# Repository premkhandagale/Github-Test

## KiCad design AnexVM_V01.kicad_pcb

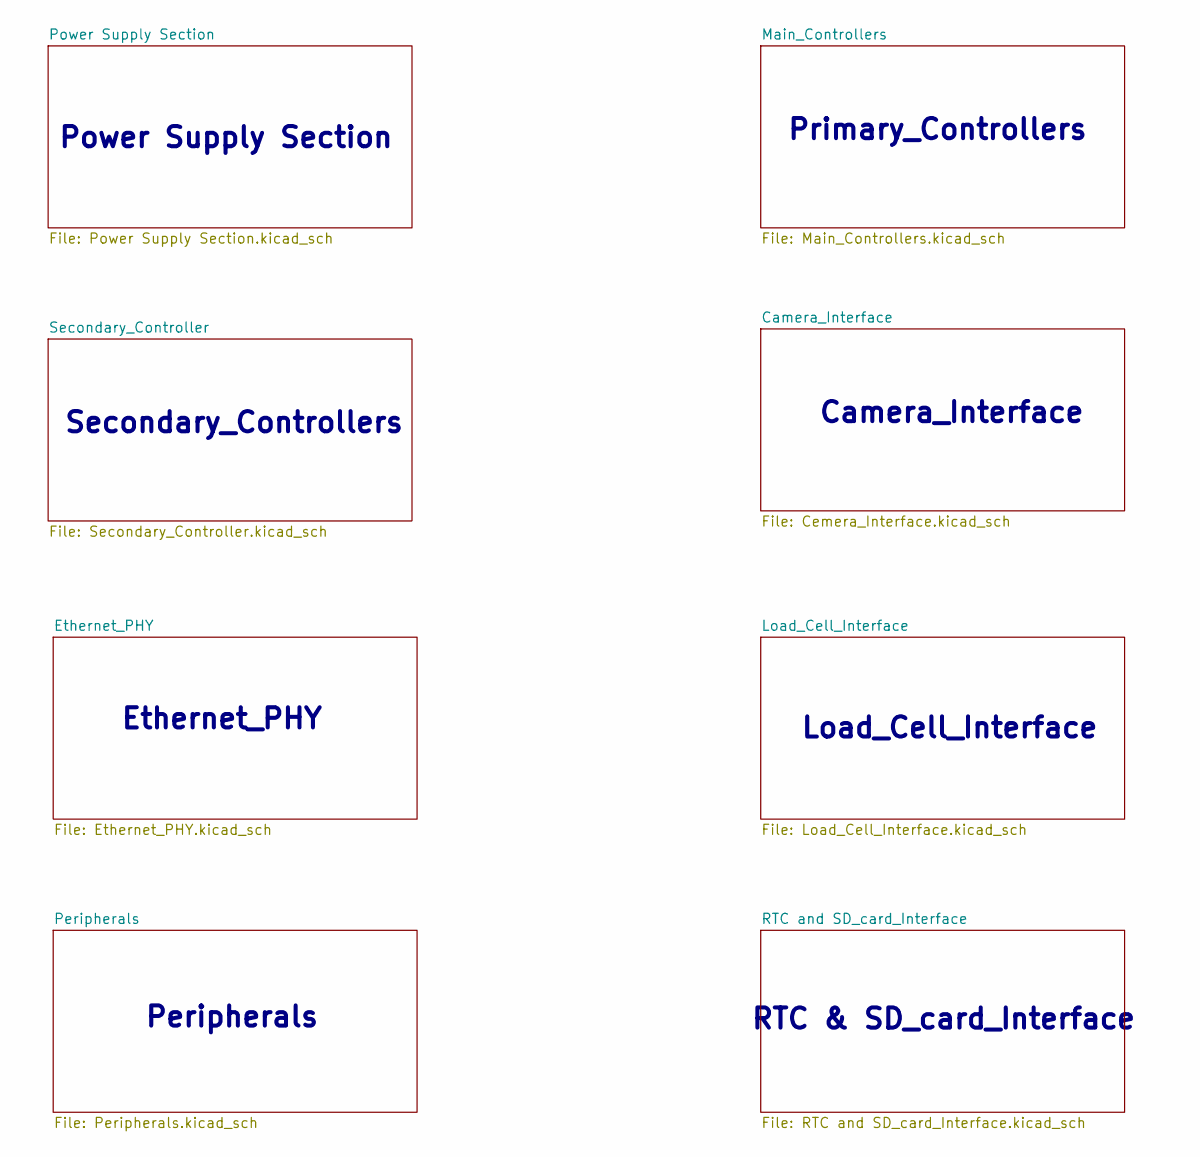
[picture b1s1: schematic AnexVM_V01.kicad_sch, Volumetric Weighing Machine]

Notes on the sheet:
Secondary_Controllers
Peripherals
Primary_Controllers
Load_Cell_Interface
Power Supply Section
Camera_Interface
Ethernet_PHY
RTC & SD_card_Interface

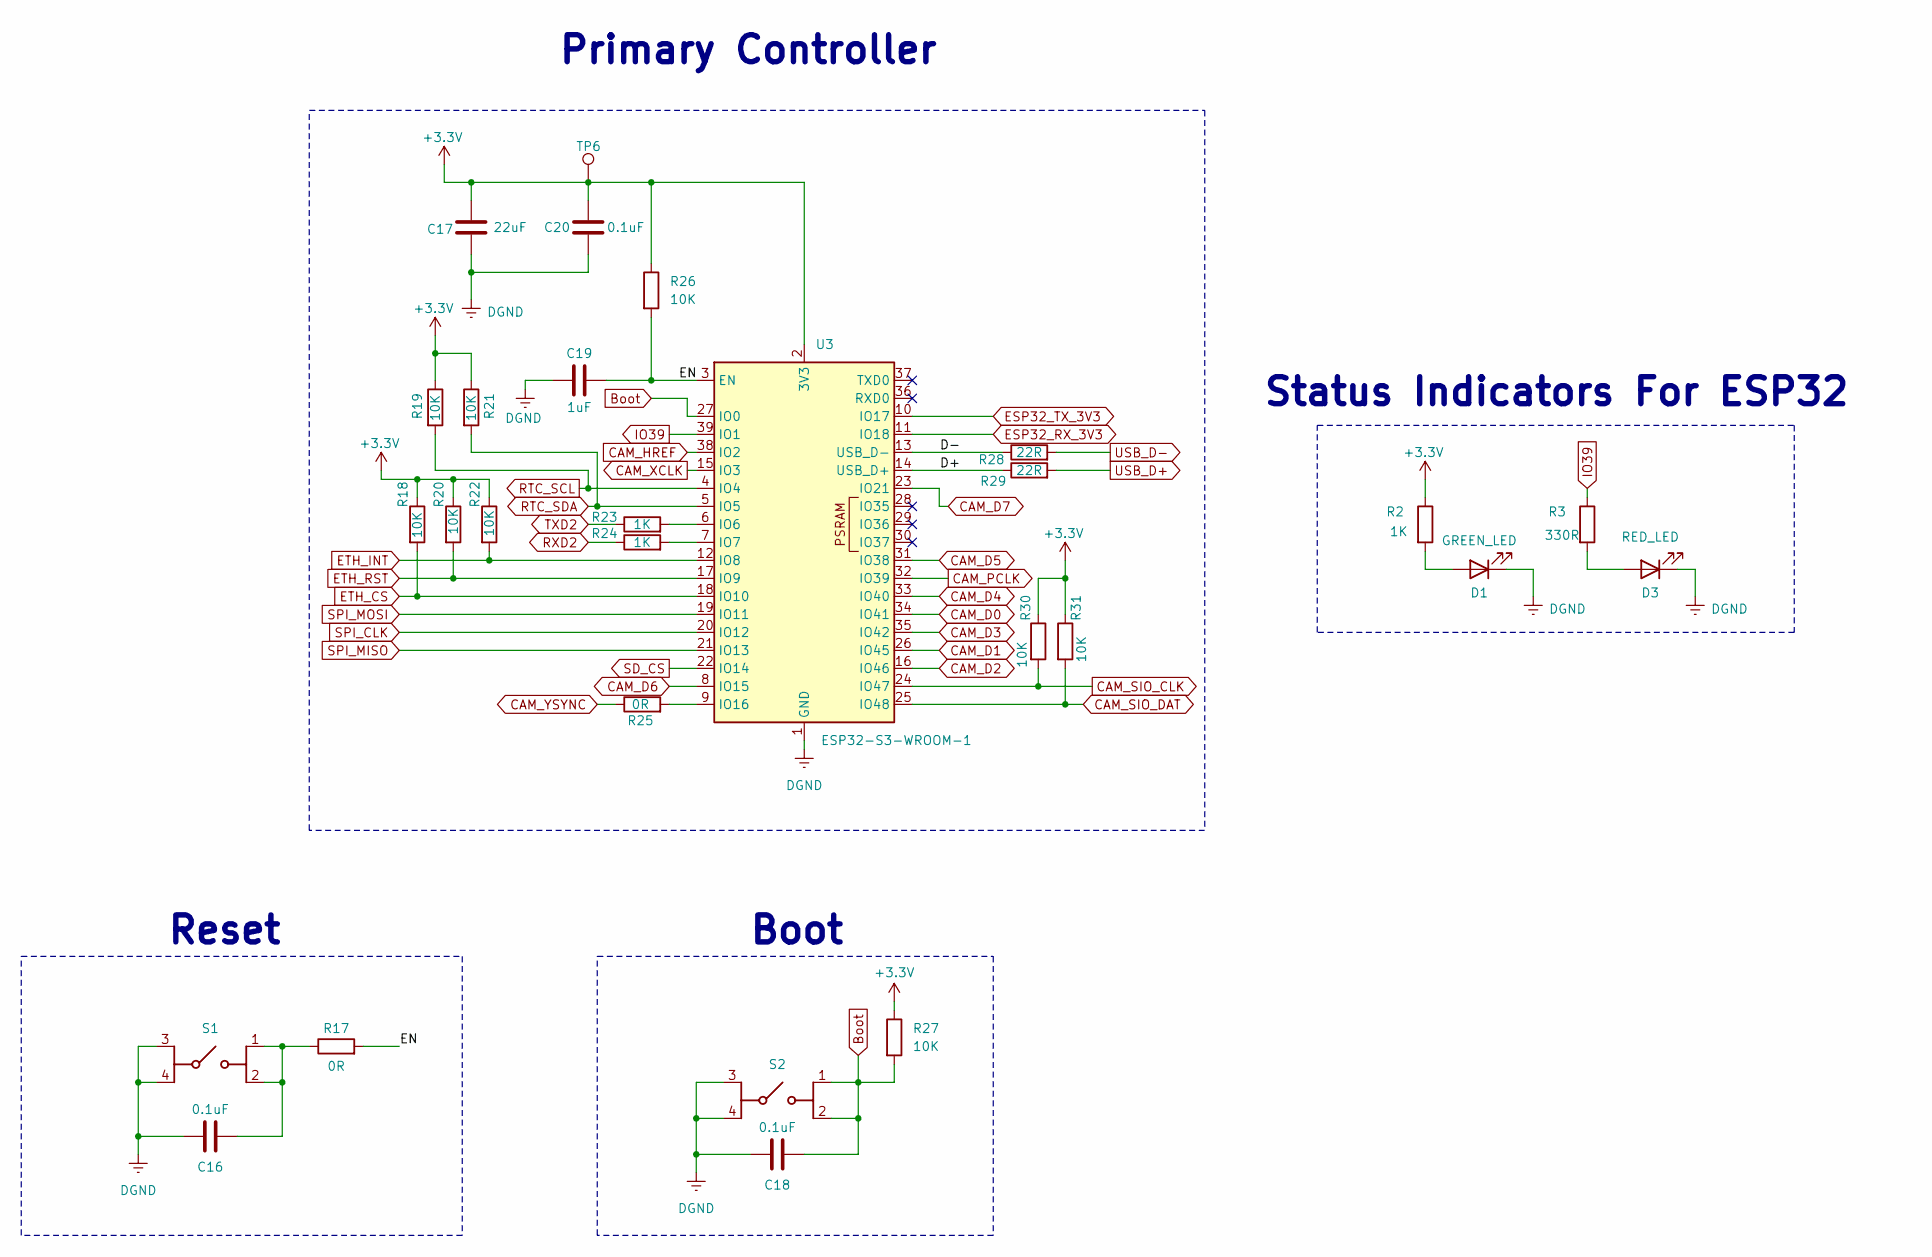
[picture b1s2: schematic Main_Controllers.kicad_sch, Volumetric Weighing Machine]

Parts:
C16, C18, C20: 0.1uF; C_0603_1608Metric
C17: 22uF; C_0805_2012Metric
C19: 1uF; C_0603_1608Metric
D1: GREEN_LED; LED_D3.0mm
D3: RED_LED; LED_D3.0mm
R2, R23, R24: 1K; R_0603_1608Metric
R3: 330R; R_0603_1608Metric
R17, R25: 0R; R_0603_1608Metric
R18, R19, R20, R21, R22, R26, R27, R30, R31: 10K; R_0603_1608Metric
R28, R29: 22R; R_0603_1608Metric
S1, S2: PTS647SK38SMTR2_LFS; SW_SPST_PTS647_Sx38; Manufacturer_Part_Number PTS647SK38SMTR2 LFS
TP6: TestPoint; TestPoint_Pad_D1.0mm
U3: ESP32-S3-WROOM-1

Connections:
+3.3V: C17.1, C20.1, R2.1, R18.1, R19.1, R20.1, R21.1, R22.1, R26.1, R27.1, R30.1, R31.1, TP6.1, U3.2 (3V3); also elsewhere on the board
/Main_Controllers/D+: R29.1, U3.14 (USB_D+)
/Main_Controllers/D-: R28.1, U3.13 (USB_D-)
/Main_Controllers/EN: C19.2, R17.2, R26.2, U3.3 (EN)
Boot: C18.2, R27.2, S2.1 (NO_1), S2.2 (NO_2), U3.27 (IO0)
CAM_D0: U3.34 (IO41); also elsewhere on the board
CAM_D1: U3.26 (IO45); also elsewhere on the board
CAM_D2: U3.16 (IO46); also elsewhere on the board
CAM_D3: U3.35 (IO42); also elsewhere on the board
CAM_D4: U3.33 (IO40); also elsewhere on the board
CAM_D5: U3.31 (IO38); also elsewhere on the board
CAM_D6: U3.8 (IO15); also elsewhere on the board
CAM_D7: U3.23 (IO21); also elsewhere on the board
CAM_HREF: U3.38 (IO2); also elsewhere on the board
CAM_PCLK: U3.32 (IO39); also elsewhere on the board
CAM_SIO_CLK: R30.2, U3.24 (IO47); also elsewhere on the board
CAM_SIO_DAT: R31.2, U3.25 (IO48); also elsewhere on the board
CAM_XCLK: U3.15 (IO3); also elsewhere on the board
CAM_YSYNC: R25.1; also elsewhere on the board
DGND: C16.1, C17.2, C18.1, C19.1, C20.2, D1.1 (K), D3.1 (K), S1.3 (COM_1), S1.4 (COM_2), S2.3 (COM_1), S2.4 (COM_2), U3.1 (GND), U3.40 (GND), U3.41 (GND); also elsewhere on the board
ESP32_RX_3V3: U3.11 (IO18); also elsewhere on the board
ESP32_TX_3V3: U3.10 (IO17); also elsewhere on the board
ETH_CS: R18.2, U3.18 (IO10); also elsewhere on the board
ETH_INT: R22.2, U3.12 (IO8); also elsewhere on the board
ETH_RST: R20.2, U3.17 (IO9); also elsewhere on the board
IO39: R3.1, U3.39 (IO1)
unnamed: D1.2 (A), R2.2
unnamed: D3.2 (A), R3.2
unnamed: C16.2, R17.1, S1.1 (NO_1), S1.2 (NO_2)
unnamed: R23.2, U3.6 (IO6)
unnamed: R24.2, U3.7 (IO7)
unnamed: R25.2, U3.9 (IO16)
RTC_SCL: R19.2, U3.4 (IO4); also elsewhere on the board
RTC_SDA: R21.2, U3.5 (IO5); also elsewhere on the board
RXD2: R24.1; also elsewhere on the board
SD_CS: U3.22 (IO14); also elsewhere on the board
SPI_CLK: U3.20 (IO12); also elsewhere on the board
SPI_MISO: U3.21 (IO13); also elsewhere on the board
SPI_MOSI: U3.19 (IO11); also elsewhere on the board
TXD2: R23.1; also elsewhere on the board
USB_D+: R29.2; also elsewhere on the board
USB_D-: R28.2; also elsewhere on the board

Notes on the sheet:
Reset
Primary Controller
Boot
Status Indicators For ESP32

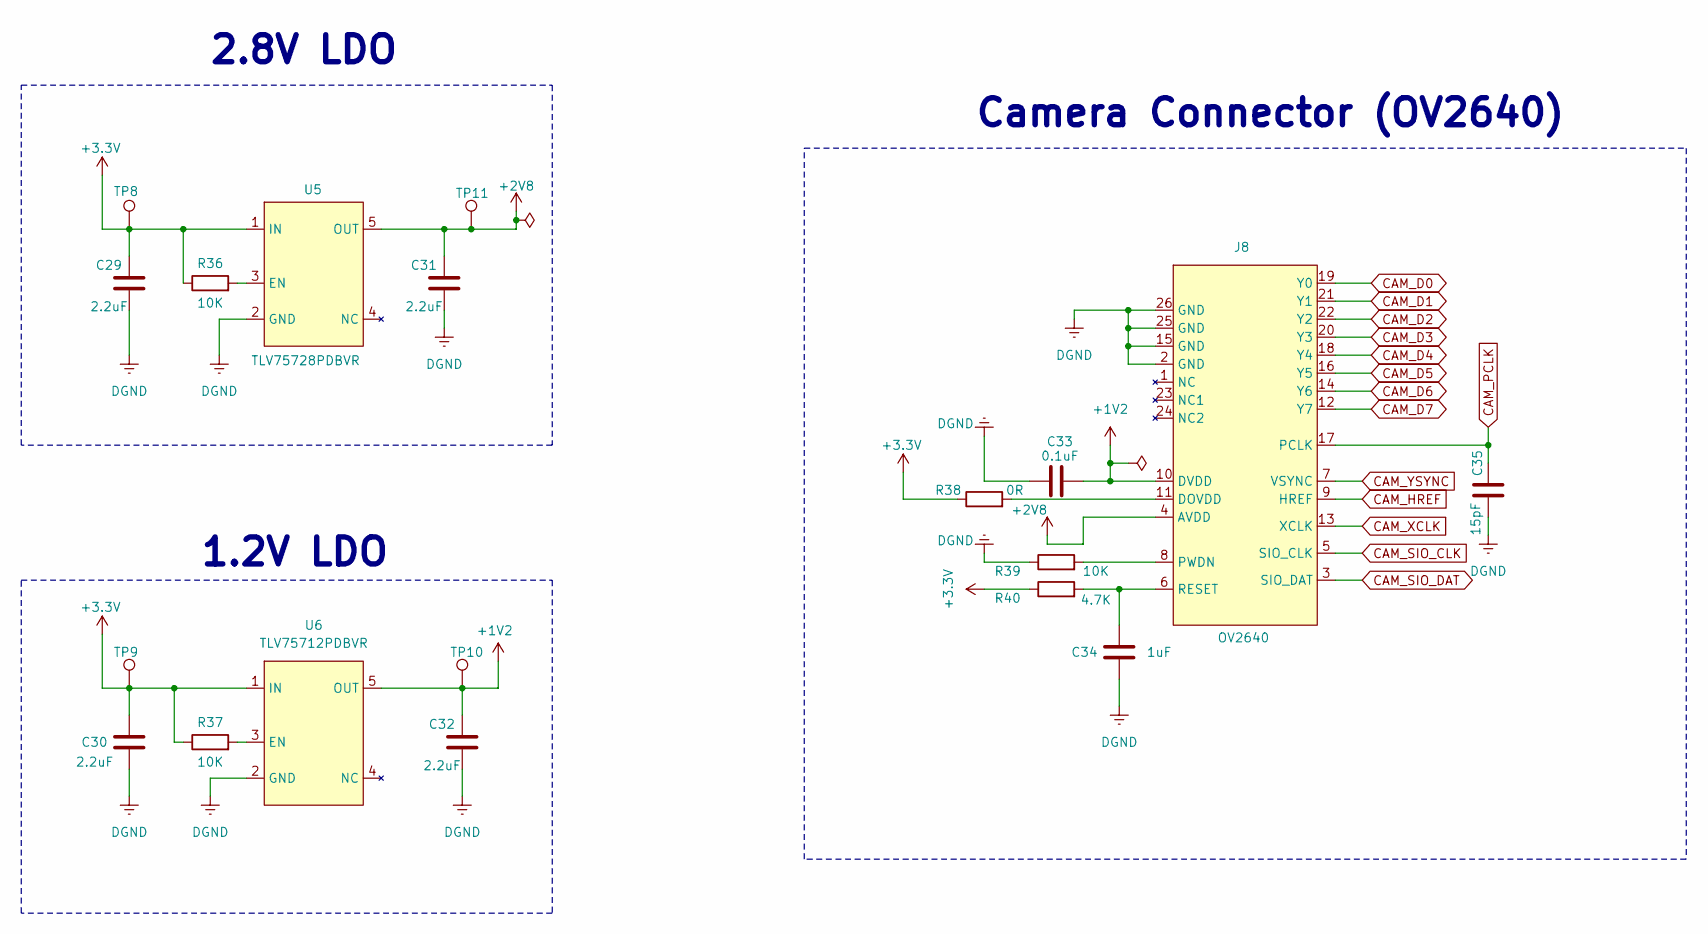
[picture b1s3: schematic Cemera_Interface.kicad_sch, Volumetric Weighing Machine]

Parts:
C29, C30, C31, C32: 2.2uF; C_0603_1608Metric
C33: 0.1uF; C_0603_1608Metric
C34: 1uF; C_0603_1608Metric
C35: 15pF; C_0603_1608Metric
J8: OV2640; Hirose_FH12-24S-0.5SH_1x24-1MP_P0.50mm_Horizontal
R36, R37, R39: 10K; R_0603_1608Metric
R38: 0R; R_0603_1608Metric
R40: 4.7K; R_0603_1608Metric
TP8, TP9, TP10, TP11: TestPoint; TestPoint_Pad_D1.0mm
U5: TLV75728PDBVR; SOT-23-5
U6: TLV75712PDBVR; SOT-23-5

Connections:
+1V2: C32.1, C33.2, J8.10 (DVDD), TP10.1, U6.5 (OUT)
+2V8: C31.1, J8.4 (AVDD), TP11.1, U5.5 (OUT)
+3.3V: C29.1, C30.1, R36.1, R37.1, R38.1, R40.1, TP8.1, TP9.1, U5.1 (IN), U6.1 (IN); also elsewhere on the board
CAM_D0: J8.19 (Y0); also elsewhere on the board
CAM_D1: J8.21 (Y1); also elsewhere on the board
CAM_D2: J8.22 (Y2); also elsewhere on the board
CAM_D3: J8.20 (Y3); also elsewhere on the board
CAM_D4: J8.18 (Y4); also elsewhere on the board
CAM_D5: J8.16 (Y5); also elsewhere on the board
CAM_D6: J8.14 (Y6); also elsewhere on the board
CAM_D7: J8.12 (Y7); also elsewhere on the board
CAM_HREF: J8.9 (HREF); also elsewhere on the board
CAM_PCLK: C35.1, J8.17 (PCLK); also elsewhere on the board
CAM_SIO_CLK: J8.5 (SIO_CLK); also elsewhere on the board
CAM_SIO_DAT: J8.3 (SIO_DAT); also elsewhere on the board
CAM_XCLK: J8.13 (XCLK); also elsewhere on the board
CAM_YSYNC: J8.7 (VSYNC); also elsewhere on the board
DGND: C29.2, C30.2, C31.2, C32.2, C33.1, C34.2, C35.2, J8.2 (GND), J8.15 (GND), J8.25 (GND), J8.26 (GND), R39.1, U5.2 (GND), U6.2 (GND); also elsewhere on the board
unnamed: J8.11 (DOVDD), R38.2
unnamed: J8.8 (PWDN), R39.2
unnamed: C34.1, J8.6 (RESET), R40.2
unnamed: R36.2, U5.3 (EN)
unnamed: R37.2, U6.3 (EN)

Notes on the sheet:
Camera Connector (OV2640)
2.8V LDO
1.2V LDO

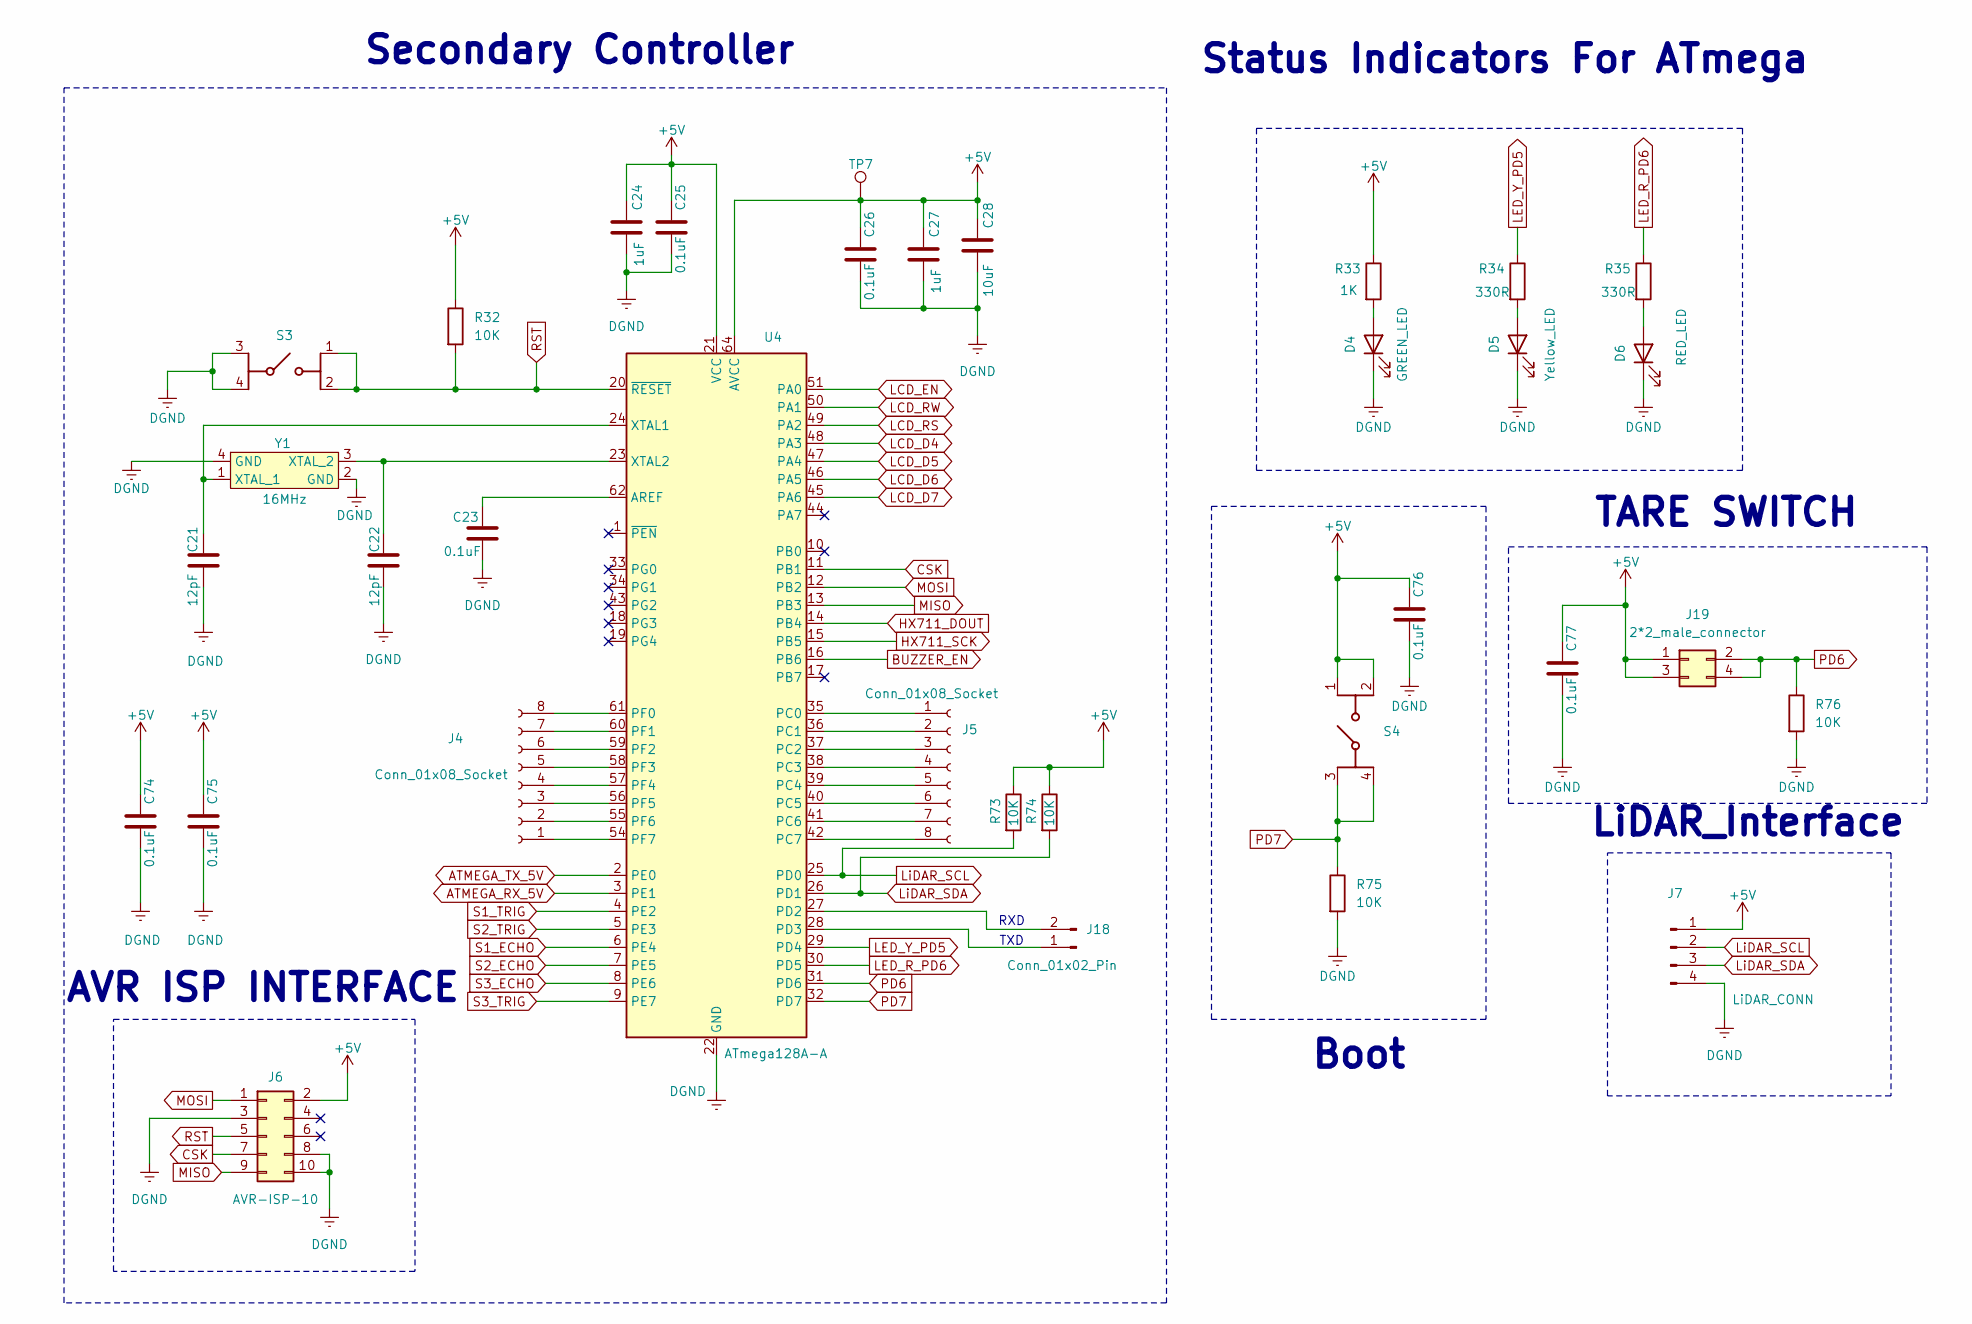
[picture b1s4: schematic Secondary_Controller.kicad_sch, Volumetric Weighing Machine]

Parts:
C21, C22: 12pF; C_0603_1608Metric
C23, C25, C26, C74, C75, C76, C77: 0.1uF; C_0603_1608Metric
C24, C27: 1uF; C_0603_1608Metric
C28: 10uF; C_0805_2012Metric
D4: GREEN_LED; LED_D3.0mm
D5: Yellow_LED; LED_D3.0mm
D6: RED_LED; LED_D3.0mm
J4, J5: Conn_01x08_Socket; PinSocket_1x08_P2.54mm_Vertical
J6: AVR-ISP-10; PinHeader_2x05_P2.54mm_Vertical
J7: LiDAR_CONN; PinHeader_1x04_P2.54mm_Vertical
J18: Conn_01x02_Pin; PinHeader_1x02_P2.54mm_Vertical
J19: 2*2_male_connector; PinHeader_2x02_P2.54mm_Vertical
R32, R73, R74, R75, R76: 10K; R_0603_1608Metric
R33: 1K; R_0603_1608Metric
R34, R35: 330R; R_0603_1608Metric
S3, S4: PTS647SK38SMTR2_LFS; SW_SPST_PTS647_Sx38; Manufacturer_Part_Number PTS647SK38SMTR2 LFS
TP7: TestPoint; TestPoint_Pad_D1.0mm
U4: ATmega128A-A; TQFP-64_14x14mm_P0.8mm
Y1: 16MHz; Crystal_SMD_3225-4Pin_3.2x2.5mm

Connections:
+5V: C24.1, C25.1, C26.1, C27.1, C28.1, C74.1, C75.1, C76.1, C77.1, J6.2 (Pin_b2), J7.1, J19.1 (NO1), J19.3 (N02), R32.1, R33.1, R73.1, R74.1, S4.1 (NO_1), S4.2 (NO_2), TP7.1, U4.21 (VCC), U4.52 (VCC), U4.64 (AVCC); also elsewhere on the board
ATMEGA_RX_5V: U4.3 (PE1); also elsewhere on the board
ATMEGA_TX_5V: U4.2 (PE0); also elsewhere on the board
BUZZER_EN: U4.16 (PB6); also elsewhere on the board
CSK: J6.7 (Pin_z8), U4.11 (PB1)
DGND: C21.2, C22.2, C23.2, C24.2, C25.2, C26.2, C27.2, C28.2, C74.2, C75.2, C76.2, C77.2, D4.1 (K), D5.1 (K), D6.1 (K), J6.3 (Pin_z4), J6.8 (Pin_b8), J6.10 (Pin_b10), J7.4, R75.2, R76.2, S3.3 (COM_1), S3.4 (COM_2), U4.22 (GND), U4.53 (GND), U4.63 (GND), Y1.2 (GND), Y1.4 (GND); also elsewhere on the board
HX711_DOUT: U4.14 (PB4); also elsewhere on the board
HX711_SCK: U4.15 (PB5); also elsewhere on the board
LCD_D4: U4.48 (PA3); also elsewhere on the board
LCD_D5: U4.47 (PA4); also elsewhere on the board
LCD_D6: U4.46 (PA5); also elsewhere on the board
LCD_D7: U4.45 (PA6); also elsewhere on the board
LCD_EN: U4.51 (PA0); also elsewhere on the board
LCD_RS: U4.49 (PA2); also elsewhere on the board
LCD_RW: U4.50 (PA1); also elsewhere on the board
LED_R_PD6: R35.1, U4.30 (PD5)
LED_Y_PD5: R34.1, U4.29 (PD4)
LiDAR_SCL: J7.2, R73.2, U4.25 (PD0)
LiDAR_SDA: J7.3, R74.2, U4.26 (PD1)
MISO: J6.9 (Pin_z10), U4.13 (PB3)
MOSI: J6.1 (Pin_z2), U4.12 (PB2)
unnamed: D4.2 (A), R33.2
unnamed: D5.2 (A), R34.2
unnamed: D6.2 (A), R35.2
unnamed: J4.1, U4.54 (PF7)
unnamed: J4.2, U4.55 (PF6)
unnamed: J4.3, U4.56 (PF5)
unnamed: J4.4, U4.57 (PF4)
unnamed: J4.5, U4.58 (PF3)
unnamed: J4.6, U4.59 (PF2)
unnamed: J4.7, U4.60 (PF1)
unnamed: J4.8, U4.61 (PF0)
unnamed: J5.1, U4.35 (PC0)
unnamed: J5.2, U4.36 (PC1)
unnamed: J5.3, U4.37 (PC2)
unnamed: J5.4, U4.38 (PC3)
unnamed: J5.5, U4.39 (PC4)
unnamed: J5.6, U4.40 (PC5)
unnamed: J5.7, U4.41 (PC6)
unnamed: J5.8, U4.42 (PC7)
unnamed: J18.1, U4.28 (PD3)
unnamed: J18.2, U4.27 (PD2)
unnamed: C23.1, U4.62 (AREF)
unnamed: C21.1, U4.24 (XTAL1), Y1.1 (XTAL_1)
unnamed: C22.1, U4.23 (XTAL2), Y1.3 (XTAL_2)
PD6: J19.2 (NC1), J19.4 (NC2), R76.1, U4.31 (PD6)
PD7: R75.1, S4.3 (COM_1), S4.4 (COM_2), U4.32 (PD7)
RST: J6.5 (Pin_z6), R32.2, S3.1 (NO_1), S3.2 (NO_2), U4.20 (~RESET)
S1_ECHO: U4.6 (PE4); also elsewhere on the board
S1_TRIG: U4.4 (PE2); also elsewhere on the board
S2_ECHO: U4.7 (PE5); also elsewhere on the board
S2_TRIG: U4.5 (PE3); also elsewhere on the board
S3_ECHO: U4.8 (PE6); also elsewhere on the board
S3_TRIG: U4.9 (PE7); also elsewhere on the board

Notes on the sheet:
Status Indicators For ATmega
Boot
RXD
TXD
Secondary Controller
TARE SWITCH
AVR ISP INTERFACE
LiDAR_Interface

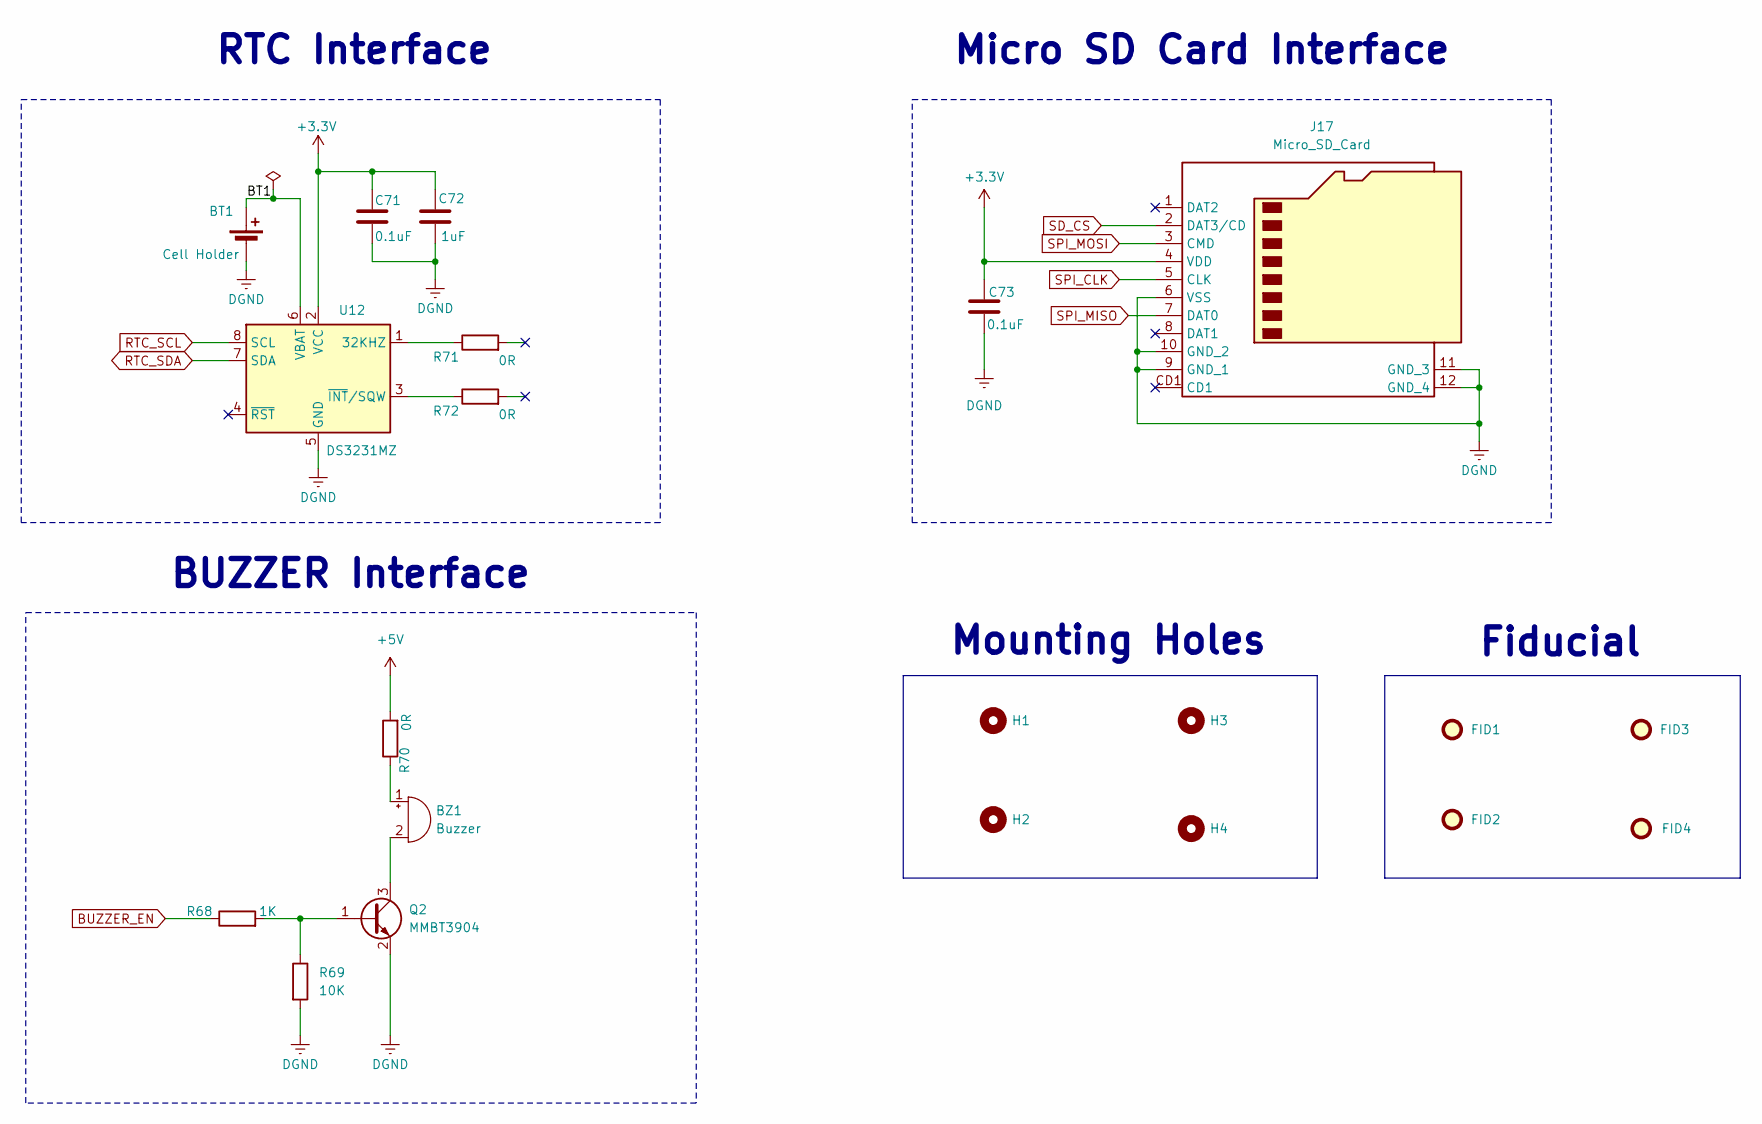
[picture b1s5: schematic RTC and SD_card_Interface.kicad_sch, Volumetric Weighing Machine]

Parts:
BT1: Cell Holder; BAT_BH-25C-1
BZ1: Buzzer; PinHeader_1x02_P2.54mm_Vertical
C71, C73: 0.1uF; C_0603_1608Metric
C72: 1uF; C_0603_1608Metric
FID1, FID2, FID3, FID4: Fiducial; Fiducial_0.5mm_Mask1mm
H1, H2, H3, H4: MountingHole; MountingHole_3mm_Pad_Via
J17: Micro_SD_Card; CUI_MSD-1-A
Q2: MMBT3904; SOT-23-3
R68: 1K; R_0603_1608Metric
R69: 10K; R_0603_1608Metric
R70, R71, R72: 0R; R_0603_1608Metric
U12: DS3231MZ; SOIC-8_3.9x4.9mm_P1.27mm

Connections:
+3.3V: C71.1, C72.2, C73.1, J17.4 (VDD), U12.2 (VCC); also elsewhere on the board
+5V: R70.2; also elsewhere on the board
/RTC and SD_card_Interface/BT1: BT1.1 (+), U12.6 (VBAT)
BUZZER_EN: R68.1; also elsewhere on the board
DGND: BT1.2 (-), C71.2, C72.1, C73.2, J17.6 (VSS), J17.9 (GND_1), J17.10 (GND_2), J17.11 (GND_3), J17.12 (GND_4), Q2.2 (E), R69.2, U12.5 (GND); also elsewhere on the board
unnamed: BZ1.1 (+), R70.1
unnamed: BZ1.2 (-), Q2.3 (C)
unnamed: Q2.1 (B), R68.2, R69.1
unnamed: R71.1, U12.1 (32KHZ)
unnamed: R72.1, U12.3 (~INT/SQW)
RTC_SCL: U12.8 (SCL); also elsewhere on the board
RTC_SDA: U12.7 (SDA); also elsewhere on the board
SD_CS: J17.2 (DAT3/CD); also elsewhere on the board
SPI_CLK: J17.5 (CLK); also elsewhere on the board
SPI_MISO: J17.7 (DAT0); also elsewhere on the board
SPI_MOSI: J17.3 (CMD); also elsewhere on the board

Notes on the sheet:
RTC Interface
Micro SD Card Interface
Mounting Holes
BUZZER Interface
Fiducial

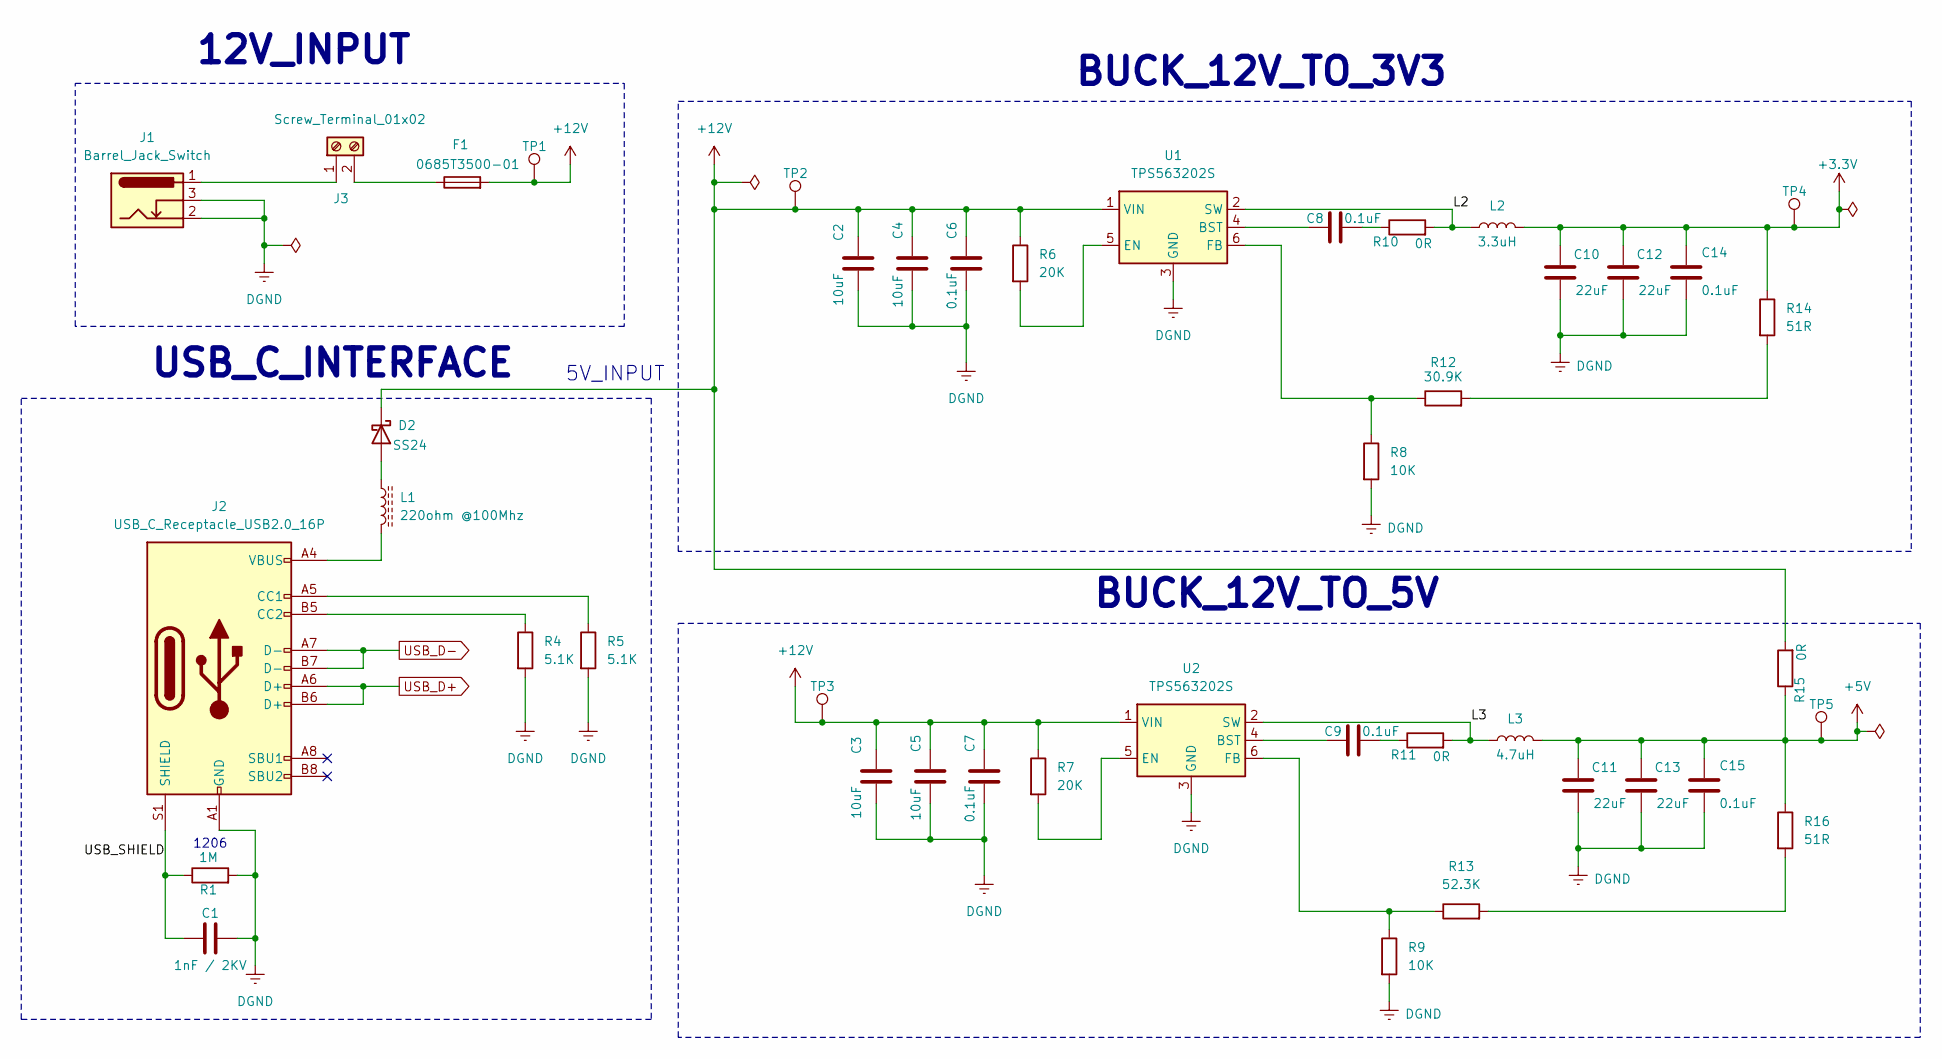
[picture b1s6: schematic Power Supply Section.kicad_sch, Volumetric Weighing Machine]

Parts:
C1: 1nF / 2KV; C_1812_4532Metric
C2, C3, C4, C5: 10uF; C_0805_2012Metric
C6, C7, C8, C9, C14, C15: 0.1uF; C_0603_1608Metric
C10, C11, C12, C13: 22uF; C_0805_2012Metric
D2: SS24; D_SMA
F1: 0685T3500-01; Fuse_1206_3216Metric
J1: Barrel_Jack_Switch; BarrelJack_GCT_DCJ200-10-A_Horizontal
J2: USB_C_Receptacle_USB2.0_16P; USB_C_Receptacle_GCT_USB4105-xx-A_16P_TopMnt_Horizontal
J3: Screw_Terminal_01x02; TerminalBlock_Xinya_XY308-2.54-2P_1x02_P2.54mm_Horizontal
L1: 220ohm @100Mhz; L_0805_2012Metric
L2: 3.3uH; L_Bourns_SRP7028A_7.3x6.6mm
L3: 4.7uH; IND_SRP6530A_BRN-M
R1: 1M; R_0603_1608Metric
R4, R5: 5.1K; R_0603_1608Metric
R6, R7: 20K; R_0603_1608Metric
R8, R9: 10K; R_0603_1608Metric
R10, R11, R15: 0R; R_0603_1608Metric
R12: 30.9K; R_0603_1608Metric
R13: 52.3K; R_0603_1608Metric
R14, R16: 51R; R_0603_1608Metric
TP1, TP2, TP3, TP4, TP5: TestPoint; TestPoint_Pad_D1.0mm
U1, U2: TPS563202S; SOT-563

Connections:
+3.3V: C10.1, C12.1, C14.1, L2.2, R14.1, TP4.1; also elsewhere on the board
+5V: C11.1, C13.1, C15.1, L3.2, R15.1, R16.1, TP5.1; also elsewhere on the board
+12V: C2.1, C3.1, C4.1, C5.1, C6.1, C7.1, D2.1 (K), F1.2, R6.1, R7.1, R15.2, TP1.1, TP2.1, TP3.1, U1.1 (VIN), U2.1 (VIN)
/Power Supply Section/L2: L2.1, R10.2, U1.2 (SW)
/Power Supply Section/L3: L3.1, R11.2, U2.2 (SW)
/Power Supply Section/USB_SHIELD: C1.1, J2.S1 (SHIELD), R1.1
DGND: C1.2, C2.2, C3.2, C4.2, C5.2, C6.2, C7.2, C10.2, C11.2, C12.2, C13.2, C14.2, C15.2, J1.2, J1.3, J2.A1 (GND), J2.A12 (GND), J2.B1 (GND), J2.B12 (GND), R1.2, R4.2, R5.2, R8.2, R9.2, U1.3 (GND), U2.3 (GND); also elsewhere on the board
unnamed: C8.2, R10.1
unnamed: C9.2, R11.1
unnamed: D2.2 (A), L1.1
unnamed: J2.A5 (CC1), R5.1
unnamed: J2.B5 (CC2), R4.1
unnamed: J2.A4 (VBUS), J2.A9 (VBUS), J2.B4 (VBUS), J2.B9 (VBUS), L1.2
unnamed: J1.1, J3.1
unnamed: F1.1, J3.2
unnamed: R12.2, R14.2
unnamed: R13.2, R16.2
unnamed: C8.1, U1.4 (BST)
unnamed: R6.2, U1.5 (EN)
unnamed: R8.1, R12.1, U1.6 (FB)
unnamed: C9.1, U2.4 (BST)
unnamed: R7.2, U2.5 (EN)
unnamed: R9.1, R13.1, U2.6 (FB)
USB_D+: J2.A6 (D+), J2.B6 (D+); also elsewhere on the board
USB_D-: J2.A7 (D-), J2.B7 (D-); also elsewhere on the board

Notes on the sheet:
1206
USB_C_INTERFACE
BUCK_12V_TO_5V
12V_INPUT
BUCK_12V_TO_3V3
5V_INPUT

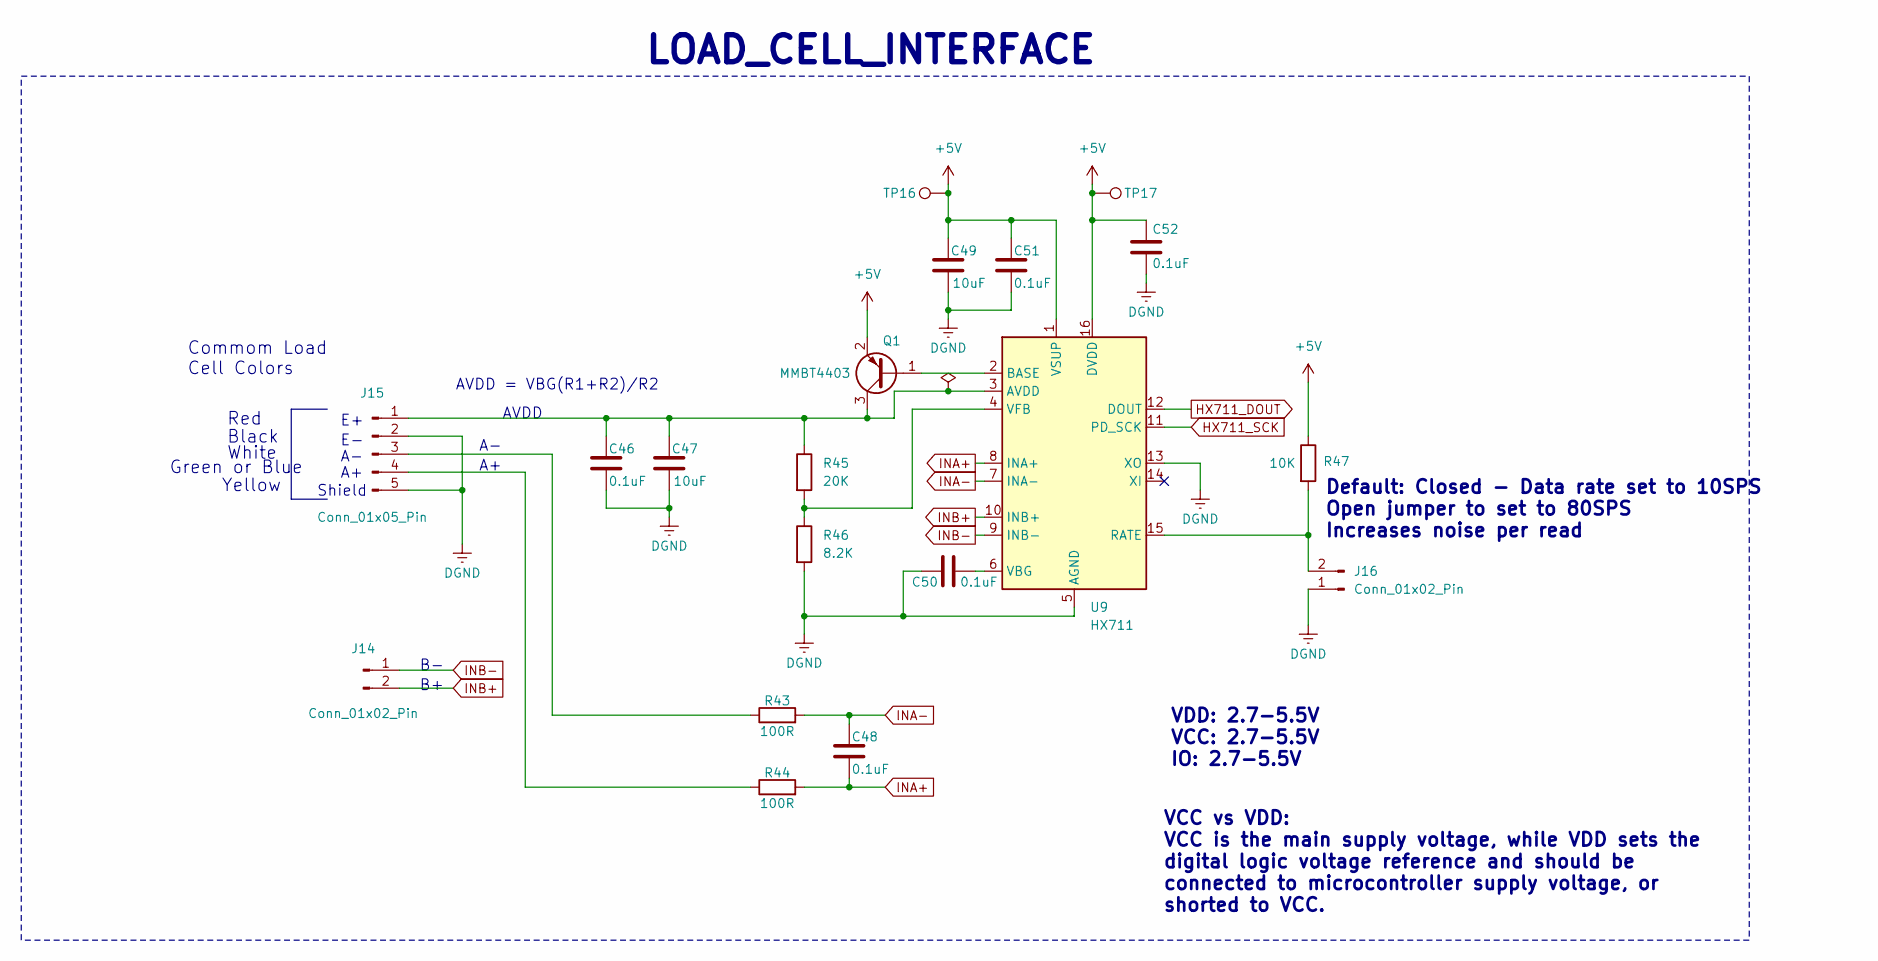
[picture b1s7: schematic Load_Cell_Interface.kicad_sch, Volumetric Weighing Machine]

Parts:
C46, C48, C50, C51, C52: 0.1uF; C_0603_1608Metric
C47, C49: 10uF; C_0805_2012Metric
J14, J16: Conn_01x02_Pin; PinHeader_1x02_P2.54mm_Vertical
J15: Conn_01x05_Pin; PinHeader_1x05_P2.54mm_Vertical
Q1: MMBT4403; SOT-23-3
R43, R44: 100R; R_0603_1608Metric
R45: 20K; R_0603_1608Metric
R46: 8.2K; R_0603_1608Metric
R47: 10K; R_0603_1608Metric
TP16, TP17: TestPoint; TestPoint_Pad_D1.0mm
U9: HX711; SOIC-16_3.9x9.9mm_P1.27mm

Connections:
+5V: C49.1, C51.1, C52.1, Q1.2 (E), R47.1, TP16.1, TP17.1, U9.1 (VSUP), U9.16 (DVDD); also elsewhere on the board
DGND: C46.2, C47.2, C49.2, C50.1, C51.2, C52.2, J15.2, J15.5, J16.1, R46.2, U9.5 (AGND), U9.13 (XO); also elsewhere on the board
HX711_DOUT: U9.12 (DOUT); also elsewhere on the board
HX711_SCK: U9.11 (PD_SCK); also elsewhere on the board
INA+: C48.2, R44.2, U9.8 (INA+)
INA-: C48.1, R43.2, U9.7 (INA-)
INB+: J14.2, U9.10 (INB+)
INB-: J14.1, U9.9 (INB-)
unnamed: C46.1, C47.1, J15.1, Q1.3 (C), R45.1, U9.3 (AVDD)
unnamed: J15.3, R43.1
unnamed: J15.4, R44.1
unnamed: J16.2, R47.2, U9.15 (RATE)
unnamed: Q1.1 (B), U9.2 (BASE)
unnamed: C50.2, U9.6 (VBG)
unnamed: R45.2, R46.1, U9.4 (VFB)

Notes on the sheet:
Green or Blue
LOAD_CELL_INTERFACE
White
Default: Closed - Data rate set to 10SPS Open jumper to set to 80SPS Increases noise per read
AVDD = VBG(R1+R2)/R2
Shield
AVDD
Red
VCC vs VDD: VCC is the main supply voltage, while VDD sets the digital logic voltage reference and should be connected to microcontroller supply voltage, or shorted to VCC.
Yellow
Commom Load Cell Colors
VDD: 2.7-5.5V VCC: 2.7-5.5V IO: 2.7-5.5V
Black
